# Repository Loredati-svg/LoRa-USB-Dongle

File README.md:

# LoRa USB Dongle

A compact USB-C LoRa dongle for the **868 MHz** EU band, built around the **STM32WLE5**.
Plug it into a PC and it enumerates as a standard **USB serial port** (CP2102N, driver-free on most OSes); the antenna connects through an **SMA** jack.

## Libraries

This project uses the shared KiCad libraries from L2-Hardware.

1. Clone the library repository **in the same parent folder as your project folders**, so that it sits next to them:

```bash
   git clone https://github.com/L2-Hardware/Kicad_Libs
```

   Expected folder structure:

```
   Kicad/
   ├── Kicad_Libs/
   ├── Project1/
   └── Project2/
   └── etc...
```
---

## Block diagram

```
USB-C ──► ESD (USBLC6-2SC6) ──► CP2102N ──UART──► STM32WLE5CCUx ──► IPD ──► RF switch ──► SMA
  │                                                (BALFHB-WL-06D3)  (BGS12WN6)
  └─► Polyfuse ──► AP2112K-3.3 LDO ──► 3V3 rail
```

## Hardware

| Block | Part | Notes |
|---|---|---|
| Connector | USB-C receptacle (USB 2.0) | 5.1 kΩ CC pull-downs, device mode |
| ESD protection | USBLC6-2SC6 | On D+/D− and VBUS |
| Input protection | Polyfuse on VBUS | |
| Power | AP2112K-3.3 | 3.3 V LDO, 600 mA |
| USB-UART bridge | CP2102N (QFN28) | TXD/RXD to the MCU UART |
| MCU + radio | STM32WLE5CCUx | Cortex-M4 + sub-GHz LoRa/(G)FSK radio, LDO mode (SMPS not used) |
| Clock | 32 MHz crystal | HSE for the radio |
| RF front-end | BALFHB-WL-06D3 + BGS12WN6 | Integrated balun/matching/harmonic filter IPD + SPDT TX/RX switch |
| Antenna | SMA jack | 50 Ω |

### RF chain

The RF section follows ST's **STDES-WL5U2ILH** reference design:

- **TX**: `RFO_LP` → series DC-block cap → IPD (harmonic filtering) → switch → SMA
- **RX**: SMA → switch → IPD (balun) → `RFI_P` / `RFI_N` (differential LNA input)
- The switch is driven by an MCU GPIO; the radio is half-duplex, so TX and RX never run at the same time.

Layout guidelines applied:
- The chip ↔ IPD section is kept as short and symmetric as possible (complex, non-50 Ω impedances).
- Everything after the IPD is a 50 Ω grounded coplanar waveguide (GCPW) with via stitching.
- Solid ground plane under the whole RF area, dedicated GND vias on every IPD ground bump.

## Tools

- **KiCad 10** — schematic and PCB

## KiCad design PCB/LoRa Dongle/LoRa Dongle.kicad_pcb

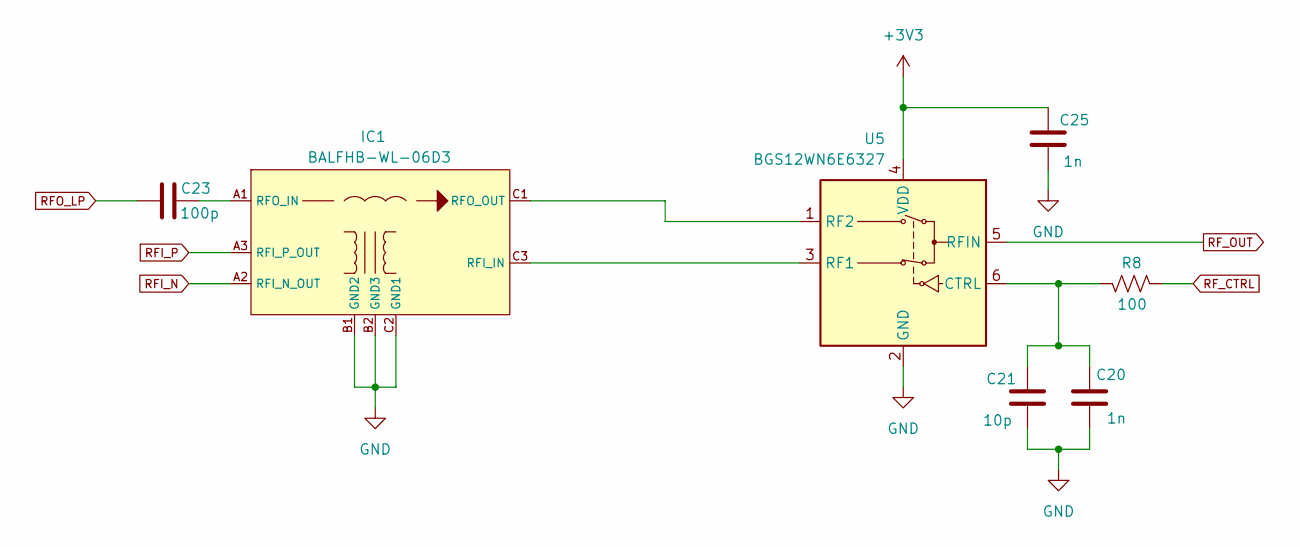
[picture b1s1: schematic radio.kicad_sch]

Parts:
C20, C25: 1n; C_0402
C21: 10p; C_0402
C23: 100p; C_0402
IC1: BALFHB-WL-06D3; BALFHBWL06D3
R8: 100; R_0402
U5: BGS12WN6E6327; Infineon_PG-TSNP-6-10_0.7x1.1mm_0.7x1.1mm_P0.4mm

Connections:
+3V3: C25.1, U5.4 (VDD); also elsewhere on the board
GND: C20.2, C21.2, C25.2, IC1.B1 (GND2), IC1.B2 (GND3), IC1.C2 (GND1), U5.2 (GND); also elsewhere on the board
unnamed: IC1.C3 (RFI_IN), U5.3 (RF1)
unnamed: C23.2, IC1.A1 (RFO_IN)
unnamed: IC1.C1 (RFO_OUT), U5.1 (RF2)
unnamed: C20.1, C21.1, R8.2, U5.6 (CTRL)
RFI_N: IC1.A2 (RFI_N_OUT); also elsewhere on the board
RFI_P: IC1.A3 (RFI_P_OUT); also elsewhere on the board
RFO_LP: C23.1; also elsewhere on the board
RF_CTRL: R8.1; also elsewhere on the board
RF_OUT: U5.5 (RFIN); also elsewhere on the board

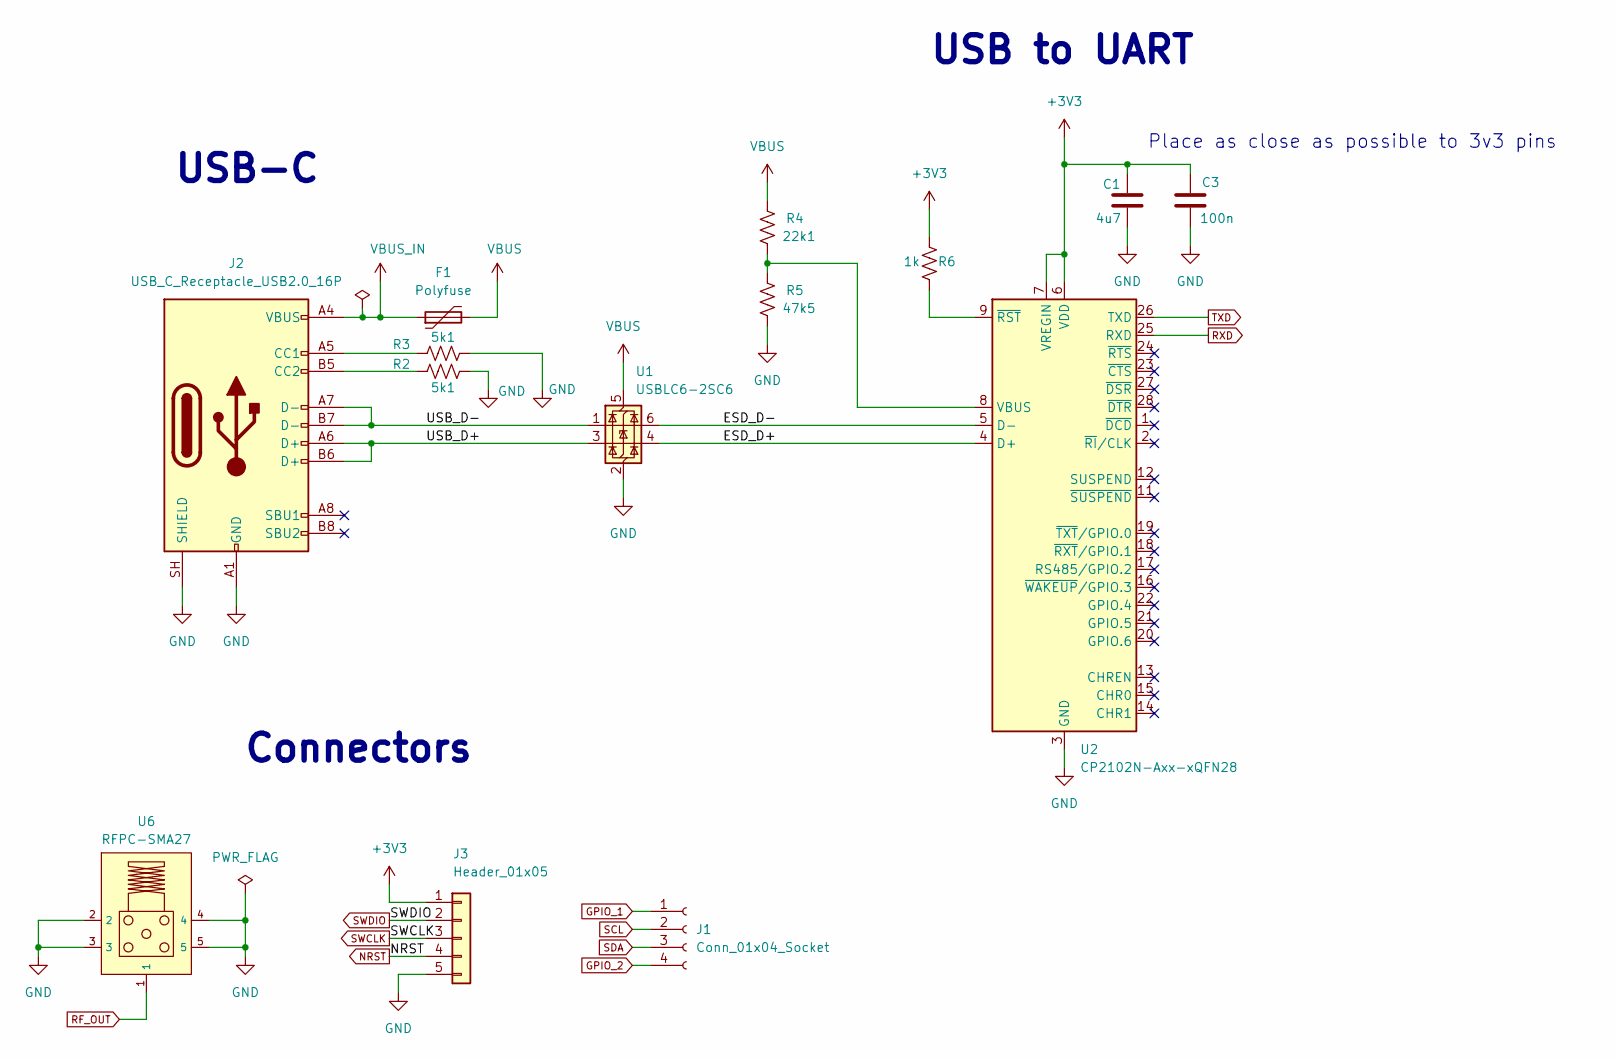
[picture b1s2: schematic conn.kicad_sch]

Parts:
C1: 4u7; C_0402
C3: 100n; C_0402
F1: Polyfuse; Fuse_1210_3225Metric
J1: Conn_01x04_Socket; PinHeader_1x04_P1.00mm_Vertical
J2: USB_C_Receptacle_USB2.0_16P; USB_C_Receptacle_GCT_USB4105-xx-A_16P_TopMnt_Horizontal
J3: Header_01x05; PinHeader_1x05_P1.00mm_Horizontal
R2, R3: 5k1; R_0402
R4: 22k1; R_0402
R5: 47k5; R_0402
R6: 1k; R_0402
U1: USBLC6-2SC6; SOT-23-6
U2: CP2102N-Axx-xQFN28; QFN-28-1EP_5x5mm_P0.5mm_EP3.35x3.35mm
U6: RFPC-SMA27; RFPCSMA27F

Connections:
+3V3: C1.1, C3.1, J3.1, R6.2, U2.6 (VDD), U2.7 (VREGIN); also elsewhere on the board
/Connectors/ESD_D+: U1.4 (I/O2), U2.4 (D+)
/Connectors/ESD_D-: U1.6 (I/O1), U2.5 (D-)
/Connectors/USB_D+: J2.A6 (D+), J2.B6 (D+), U1.3 (I/O2)
/Connectors/USB_D-: J2.A7 (D-), J2.B7 (D-), U1.1 (I/O1)
GND: C1.2, C3.2, J2.A1 (GND), J2.A12 (GND), J2.B1 (GND), J2.B12 (GND), J2.SH (SHIELD), J3.5, R2.2, R3.2, R5.2, U1.2 (GND), U2.3 (GND), U2.29 (GND), U6.2, U6.3, U6.4, U6.5; also elsewhere on the board
GPIO_1: J1.1; also elsewhere on the board
GPIO_2: J1.4; also elsewhere on the board
NRST: J3.4; also elsewhere on the board
unnamed: J2.A5 (CC1), R3.1
unnamed: J2.B5 (CC2), R2.1
unnamed: R4.2, R5.1, U2.8 (VBUS)
unnamed: R6.1, U2.9 (~RST)
RF_OUT: U6.1; also elsewhere on the board
RXD: U2.25 (RXD); also elsewhere on the board
SCL: J1.2; also elsewhere on the board
SDA: J1.3; also elsewhere on the board
SWCLK: J3.3; also elsewhere on the board
SWDIO: J3.2; also elsewhere on the board
TXD: U2.26 (TXD); also elsewhere on the board
VBUS: F1.2, R4.1, U1.5 (VBUS); also elsewhere on the board
VBUS_IN: F1.1, J2.A4 (VBUS), J2.A9 (VBUS), J2.B4 (VBUS), J2.B9 (VBUS)

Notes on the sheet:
USB-C
USB to UART
Connectors
Place as close as possible to 3v3 pins

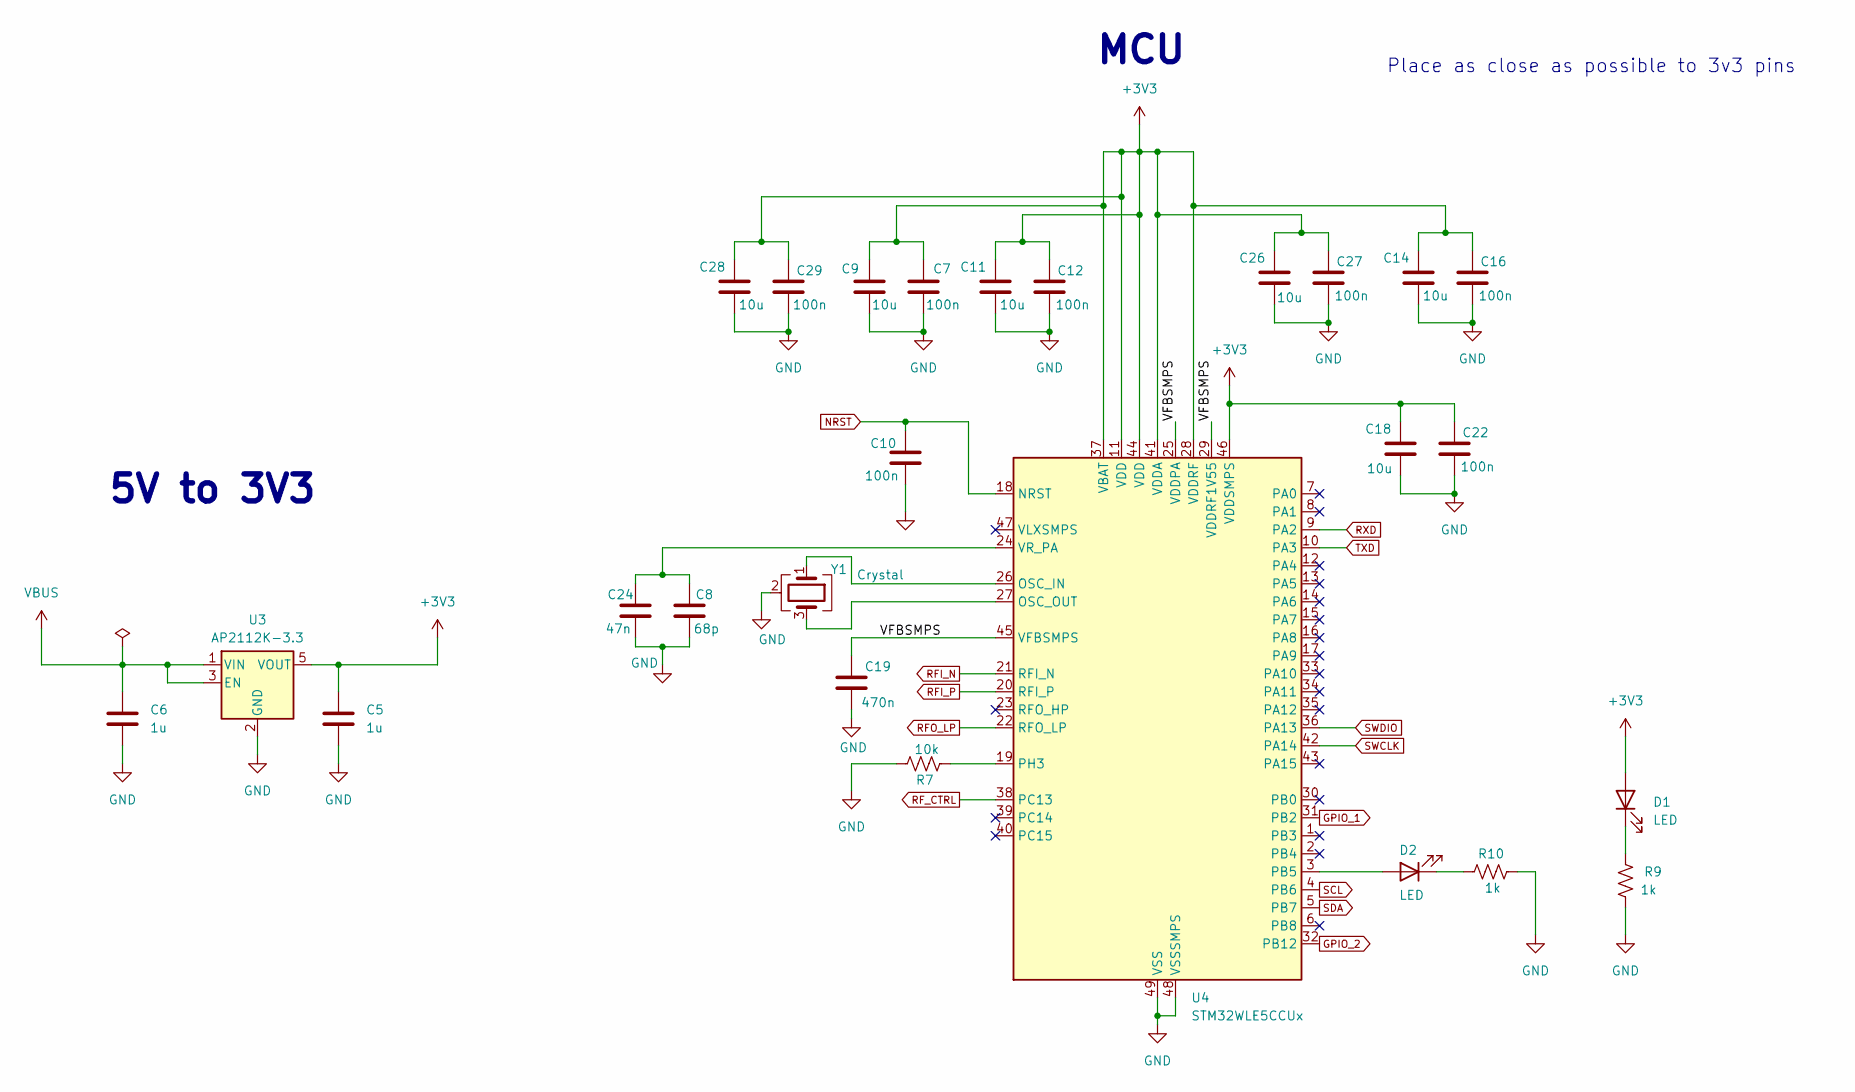
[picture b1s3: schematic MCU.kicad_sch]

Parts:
C5, C6: 1u; C_0402
C7, C10, C12, C16, C22, C27, C29: 100n; C_0402
C8: 68p; C_0402
C9, C11, C14, C18, C26, C28: 10u; C_0402
C19: 470n; C_0402
C24: 47n; C_0402
D1, D2: LED; LED_0603_1608Metric
R7: 10k; R_0402
R9, R10: 1k; R_0402
U3: AP2112K-3.3; SOT-23-5
U4: STM32WLE5CCUx; QFN-48-1EP_7x7mm_P0.5mm_EP5.6x5.6mm
Y1: Crystal; Crystal_SMD_2016-4Pin_2.0x1.6mm

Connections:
+3V3: C5.1, C7.1, C9.1, C11.1, C12.1, C14.1, C16.1, C18.1, C22.1, C26.1, C27.1, C28.1, C29.1, D1.2 (A), U3.5 (VOUT), U4.11 (VDD), U4.28 (VDDRF), U4.37 (VBAT), U4.41 (VDDA), U4.44 (VDD), U4.46 (VDDSMPS); also elsewhere on the board
/MCU/VFBSMPS: C19.1, U4.25 (VDDPA), U4.29 (VDDRF1V55), U4.45 (VFBSMPS)
GND: C5.2, C6.2, C7.2, C8.2, C9.2, C10.2, C11.2, C12.2, C14.2, C16.2, C18.2, C19.2, C22.2, C24.2, C26.2, C27.2, C28.2, C29.2, R7.1, R9.2, R10.2, U3.2 (GND), U4.48 (VSSSMPS), U4.49 (VSS), Y1.2 (G), Y1.4 (G); also elsewhere on the board
GPIO_1: U4.31 (PB2); also elsewhere on the board
GPIO_2: U4.32 (PB12); also elsewhere on the board
NRST: C10.1, U4.18 (NRST); also elsewhere on the board
unnamed: D1.1 (K), R9.1
unnamed: D2.2 (A), U4.3 (PB5)
unnamed: D2.1 (K), R10.1
unnamed: U4.26 (OSC_IN), Y1.1
unnamed: U4.27 (OSC_OUT), Y1.3
unnamed: R7.2, U4.19 (PH3)
unnamed: C8.1, C24.1, U4.24 (VR_PA)
RFI_N: U4.21 (RFI_N); also elsewhere on the board
RFI_P: U4.20 (RFI_P); also elsewhere on the board
RFO_LP: U4.22 (RFO_LP); also elsewhere on the board
RF_CTRL: U4.38 (PC13); also elsewhere on the board
RXD: U4.9 (PA2); also elsewhere on the board
SCL: U4.4 (PB6); also elsewhere on the board
SDA: U4.5 (PB7); also elsewhere on the board
SWCLK: U4.42 (PA14); also elsewhere on the board
SWDIO: U4.36 (PA13); also elsewhere on the board
TXD: U4.10 (PA3); also elsewhere on the board
VBUS: C6.1, U3.1 (VIN), U3.3 (EN); also elsewhere on the board

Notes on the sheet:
Place as close as possible to 3v3 pins
MCU
5V to 3V3

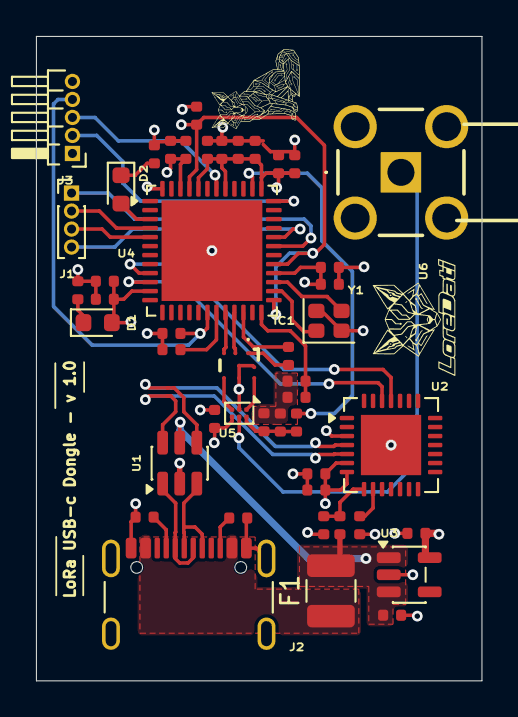
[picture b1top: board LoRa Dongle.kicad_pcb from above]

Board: 4 copper layers, 24.8 x 35.8 mm, 47 parts (0 on the bottom side), 38 nets.

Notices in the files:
README.md:
License: CERN-OHL-P
